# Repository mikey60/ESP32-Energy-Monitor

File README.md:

# ESP32-Energy-Monitor
Hardware and code are designed to use the Aeon labs Home Energy Meter, model DSB09104-zwus, current clamps and housing.  I was frustrated with the occasional intermittent connection of the Aeon Labs Home Energy meter because the Z-Wave hub and energy meter were two floors apart.  Also the energy meter would occasionally give very high erroneous readings.  The unit did not work at all after I upgraded the firmware. That is what led to the ESP32 energy monitor project.

**Features:**
* Uses Aeon labs DSB09104-zwus current clamps and housing
* Wifi has increased signal strength over Z-Wave
* Uses a minimum amount of components
* Calculates real power like residential energy meters
* The capability of calculating power factor could be added
* Can easily adjust the scale factors to get agreement with energy company's meter
* Can debug using WiFi and telnet
* Can download new code Over The Air (OTA)

**Disadvantages:**
* The power supply is old school with a 60Hz transformer with a diode bridge and 1000uF capacitor to provide the DC power and the 60 Hz AC signal to the energy meter.  I picked up the 6 volt DC, 800mA class 2 power supply at the local surplus store.  I opened the power supply to add the two wires for the sine wave input to the energy monitor.  I also added two 1 amp rectifier diodes in series with the filtered DC output to the reduce the power of the AMS1117-3.3 LDO regulator on the energy monitor board.
* There is some distortion of the sine wave voltage due to the load on the power supply.
* The output of the current clamps is also distorted especially at low currents. The linearity of the output versus power is not too bad even with the distortion.
* The WiFi activity adds some noise to  the A/D coversions.
* The energy totals get reset if there is a wifi problem or power interruption. Additonal code could be written to keep a running sum in Flash every so often.

**PCB**

The KiCad PCB files can be found in the PCB folder including a PDF file of the schematic and layout.
There are two modifications that I made to the hardware design that are not shown in the documentation of the PCB folder.

Modifications
* I added a 22uF capacitor directly across the output and ground pins of the AMS1117-3.3 LDO regulator to stop the output oscillation.  The other 22uF capacitor on the 3.3 volt output of the LDO regulator is close to the ESP32. 
* I addded a 200pF capacitor and a 100 ohm resistor to the op amp circuit that provides the 3.3/2 volt virtual ground to provide stability when driving a capacitive load.  The output would oscillate when a 1x probe (120pF capacitance) was touched to the output.  The Micro-Cap 12 stability analysis showed that the circuit should be stable with a 120pF capacitor.  See 'Stability Analysis' in the data folder. Maybe there is other capacitances I am not accounting for or maybe the LMC6484 op amp I purchased on ebay is deficient in the stability performance area.  The Micro-Cap file is also in the data folder.  By the way, the Micro-cap 12 simulator is now free. 

**Other Information**

* Pictures of the finished device can be found in the images folder.
* A plot of the current consumption of the device can be found in the data folder.
* I attached a logic analyzer  to pin IO4 and let it run for an hour and did not see any missed 1 KHz samples

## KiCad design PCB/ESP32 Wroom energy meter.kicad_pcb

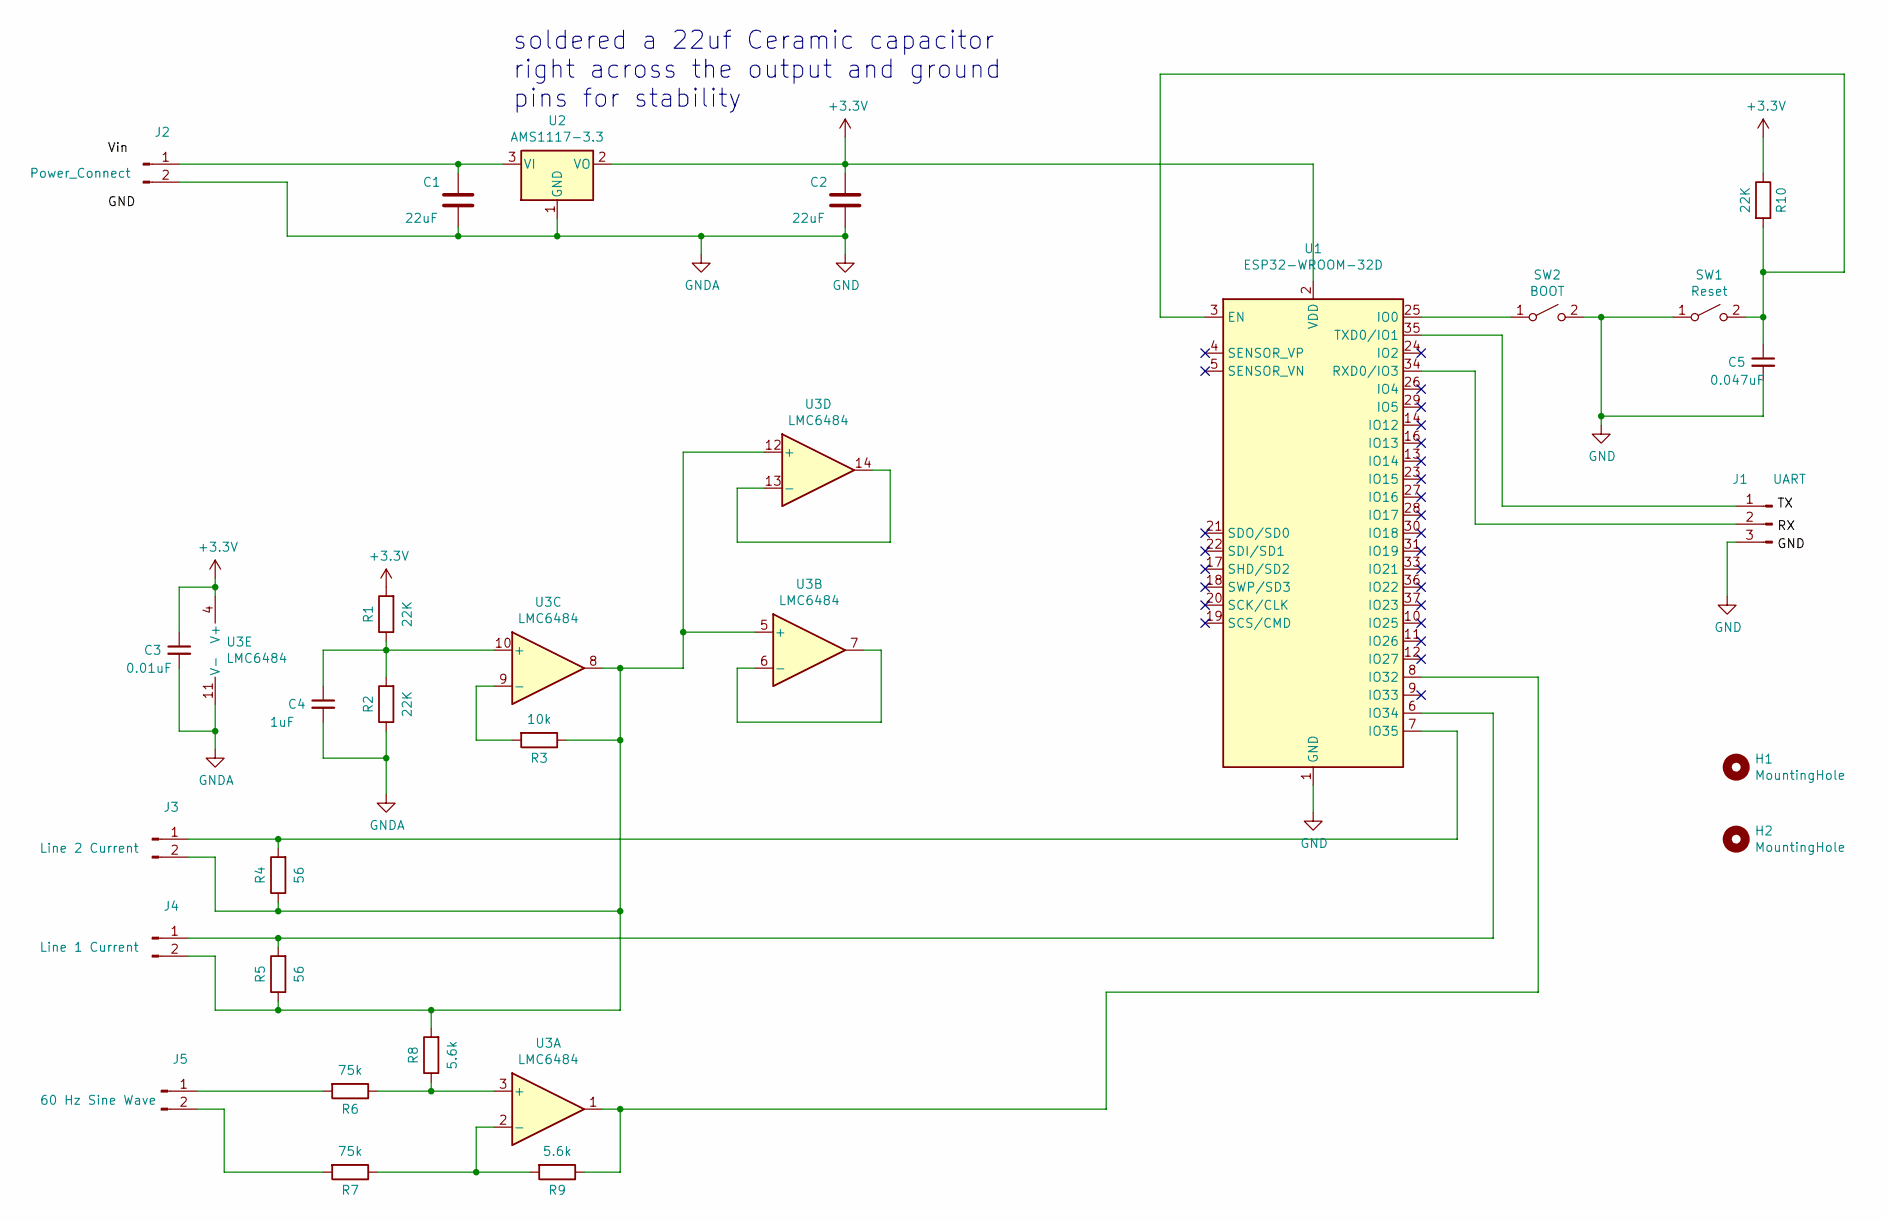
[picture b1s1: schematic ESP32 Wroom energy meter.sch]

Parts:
C1, C2: 22uF; C_1206_3216Metric_Pad1.42x1.75mm_HandSolder
C3: 0.01uF; C_0805_2012Metric_Pad1.15x1.40mm_HandSolder
C4: 1uF; C_0805_2012Metric_Pad1.15x1.40mm_HandSolder
C5: 0.047uF; C_0805_2012Metric_Pad1.15x1.40mm_HandSolder
H1, H2: MountingHole; MountingHole_2mm
J1: UART; PinHeader_1x03_P2.54mm_Vertical
J2: Power_Connect; PinHeader_1x02_P2.54mm_Vertical
J3: Line 2 Current; PinHeader_1x02_P2.54mm_Vertical
J4: Line 1 Current; PinHeader_1x02_P2.54mm_Vertical
J5: 60 Hz Sine Wave; PinHeader_1x02_P2.54mm_Vertical
R1, R2, R10: 22K; R_0805_2012Metric_Pad1.15x1.40mm_HandSolder
R3: 10k; R_0805_2012Metric_Pad1.15x1.40mm_HandSolder
R4, R5: 56; R_0805_2012Metric_Pad1.15x1.40mm_HandSolder
R6, R7: 75k; R_0805_2012Metric_Pad1.15x1.40mm_HandSolder
R8, R9: 5.6k; R_0805_2012Metric_Pad1.15x1.40mm_HandSolder
SW1: Reset; SW_SPST_EVQPE1
SW2: BOOT; SW_SPST_EVQPE1
U1: ESP32-WROOM-32D; ESP32-WROOM-32
U2: AMS1117-3.3; SOT-223-3_TabPin2
U3: LMC6484; SOIC-14_3.9x8.7mm_P1.27mm

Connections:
+3V3: C2.1, C3.1, R1.2, R10.1, U1.2 (VDD), U2.2 (VO), U3.4 (V+)
GND: C1.2, C2.2, C3.2, C4.2, C5.2, J1.3, J2.2, R2.1, SW1.1 (A), SW2.2 (B), U1.1 (GND), U1.15 (GND), U1.38 (GND), U1.39 (GND), U2.1 (GND), U3.11 (V-)
unnamed: C1.1, J2.1, U2.3 (VI)
unnamed: C4.1, R1.1, R2.2, U3.10 (+)
unnamed: C5.1, R10.2, SW1.2 (B), U1.3 (EN)
unnamed: J1.1, U1.35 (TXD0/IO1)
unnamed: J1.2, U1.34 (RXD0/IO3)
unnamed: J3.1, R4.2, U1.7 (IO35)
unnamed: J3.2, J4.2, R3.1, R4.1, R5.1, R8.2, U3.5 (+), U3.8, U3.12 (+)
unnamed: J4.1, R5.2, U1.6 (IO34)
unnamed: J5.1, R6.2
unnamed: J5.2, R7.2
unnamed: R3.2, U3.9 (-)
unnamed: R6.1, R8.1, U3.3 (+)
unnamed: R7.1, R9.2, U3.2 (-)
unnamed: R9.1, U1.8 (IO32), U3.1
unnamed: SW2.1 (A), U1.25 (IO0)
unnamed: U3.6 (-), U3.7
unnamed: U3.13 (-), U3.14

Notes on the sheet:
soldered a 22uf Ceramic capacitor right across the output and ground pins for stability

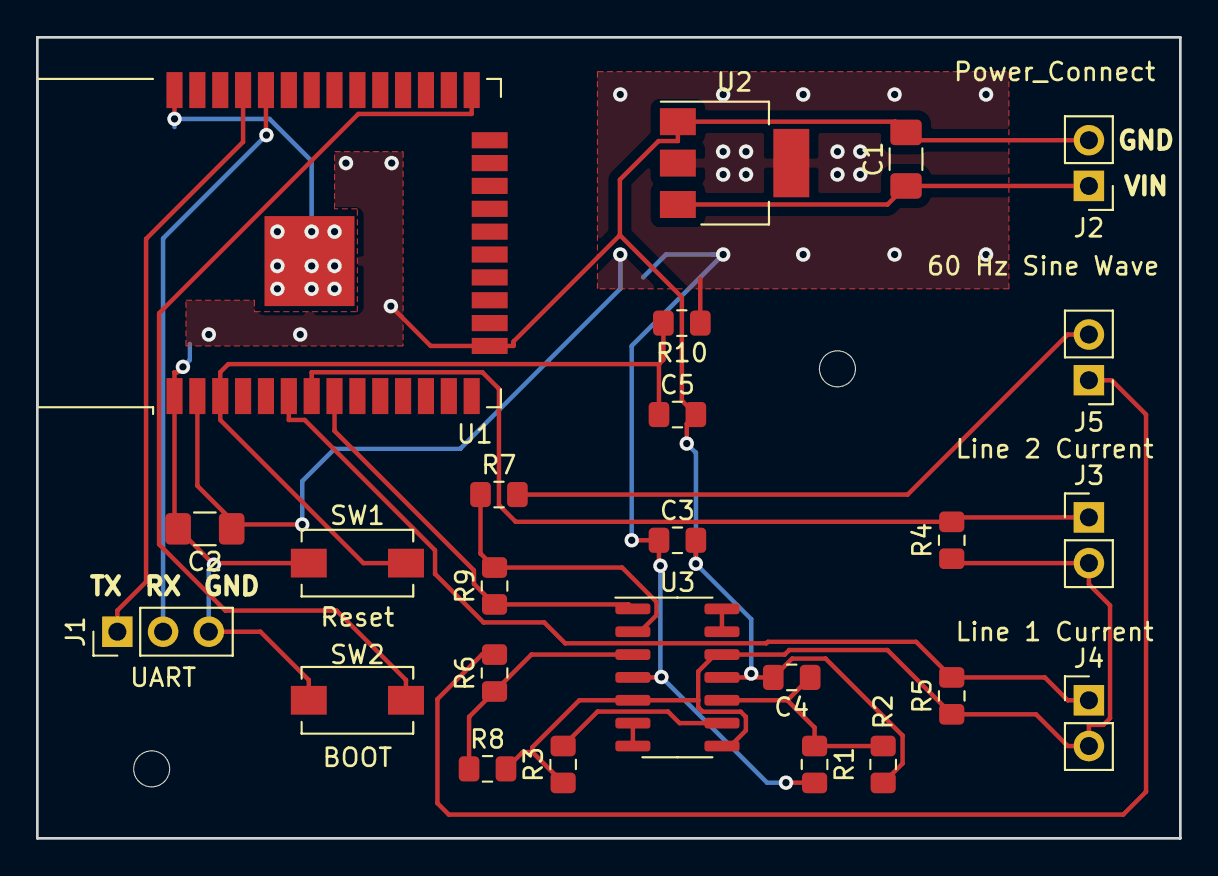
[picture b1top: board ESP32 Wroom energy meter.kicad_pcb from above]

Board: 2 copper layers, 63.5 x 44.5 mm, 27 parts (0 on the bottom side), 19 nets.

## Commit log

2020-05-22 Master
2020-05-22 First release
2020-05-23 Added PCB design
2020-11-20 Initial Release
2020-11-21 Some minor updates
2021-03-05 reduce size of images
